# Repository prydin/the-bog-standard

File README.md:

# The Bog Standard - A common sense 50W amplifier for the common (wo)man.

## Background
The idea of this amplifier came from me seeing beginners struggling with amplifier designs 
that were either pure junk, too complicated, required exotic and obsolete components or all of the above.
This sparked a very interesting conversation on diyaudio.com where I presented a previous design
as a candidate. Over the next few weeks, that design got thoroughly critiqued and reworked several times.
As the keen reader will see, the design eventually gravitated towards an architecture that closely
resembles Douglas Self's famous "Blameless Amplifier" concept, albeit using MOSFET output devices rather
than BJTs. 

## Design goals
I had a few overall requirements of the design:
1. Respectable HiFi-grade performance
2. Using only basic, readily available components
3. Being forgiving with respect to component matching
4. No complicated cooling or power supplies needed
5. Being simple enough that someone with modest electronics knowledge can understand its operating principles.

## Component choices
I went with MOSFET output devices because I like the way they sound and they're easy to work with. While
some people suggested rare and expensive lateral MOSFETs, in the spirit of the project, I went with the
good old IRFP(9)240. Based on measurements and listening tests, they perform very well in this setup.

The rest of the transistors are, well, bog standard: 2N5551/2N5401 for low power and BD139/140 for 
medium power. That's it. The rest are just passives and basic diodes.

## Design highlights
As mentioned above, the design follows Doug Self's Blameless Amplifier relatively closely. I went with 
a fairly high loop gain to make sure I had enough to smooth out any non-linearities in the MOSFETs. But
even with all that gain, the amplifier is stable with a 47pF Cdom (and probably 33pF as well, but I was 
out of that value when I tested it). SPICE simulations show about 90 degrees of phase margin with 33pF.

The rest is, you guessed it, Bog Standard. A long-tailed pair differential amplifier at the input section,
a simple single-ended VAS, BJT drivers and MOSFET outputs. The input section and VAS are driven by constant
current sources and the LTP is loaded using a current mirror. The current through the LTP is about 1mA and 
the VAS runs on about 13mA. Q15 offers some basic SOA protection of the VAS. 

The quiescent current is regulated using a standard VBE multiplier controlled by a simple voltage divider.
The design calls for the VBE transistor to be thermally connected to the output devices, by means of 
mounting them on the same heat sink. This gives the amplifier a negative temperature coefficient. 

## Quiescent current setting
I am tentatively running the amplifier on 100mA of quiescent current. This results in an overall power draw
of slighly more than 3W, which seems like a reasonable compromise. Increasing the bias above this didn't 
seem to have any meaningful impact on distortion.

It is very important to let the amplifier warm up before fine tuning the bias. With the VBE multiplier
mounted close to the drivers and outputs, the bias current will have a pronounced negative temperature 
coefficient, so you should expect the quiescent current to be higher on a cold amplifier and then settle.

## Volume control
It's crucial to fit the volume control after the input lowpass filter in order to avoid a frequency response
that varies with the volume. To facilitate this, the PCB comes with a connector for a volume potentiometer. 
I've used 50k pots with good results. If you don't need a volume control at the power amplifier, i.e.
if the amplifier is driven by a preamp, just short pins 2 and 3 on the volume control connector.

## Power supply and grounding
The very simple unregulated power supply that's part of this repository seems to work well and is desined
along the principle of simplicity rather than sophistication. The amplifier itself should have a decent Power
Supply Rejection Ratio (PSRR).

In my build, all grounds (signal, earth and power) meet at the DC side of the power supply and the PCB layout provides
connectors for tying the grounds together. In preliminary tests, there was no audible hum or noise. 

## Transformer
I recommend a 160VA/2x25V toroidial transformer. The actual secondary voltage will vary depending on your mains
voltage, but where I live I get about 35V DC on each rail after rectification. This results in clipping at about
95W in my case, so there's plenty of headroom for the rated 50W. I don't think it would survive sustained 95W power,
at least not without a much larger heatsink than what I have. 

## Case and hardware
The PCBs are compact, so you have a lot of freedom in terms of your physical build. I went for a compact
case from NobSound. It made wire routing a bit challenging and I had to make some compromises. However, the
build came out great without any audible hum or noise. 

### Heat sinks
I'm using a pair of 100 x 40 x 20mm finned heatsinks I found on Amazon. They work well up to about 40W but
get very hot at 50W and above. If your case allows it, I would recommend slightly larger sinks. This is one 
of those situations where bigger really IS better!

## Preliminary performance metrics
* THD @ 1W/1kHz: <0.005%
* Bandwidth (3dB): 20Hz - 900kHz
* Slew rate: 27V/us
* Calculated phase margin: 89 degrees

## Schematic
Click image to enlarge!

## Gerber files
* Amplifier: [kicad/gerber](kicad/gerber)
* Power supply: [kicad/power_supply/gerber](kicad/power_supply/gerber)

## Image gallery

## Contributing
If you find any errors in the design, or if you have ideas how it can be improved, please create an issue report in Github (top menu).
Or even better, clone the repo and issue a PR with your changes and I will consider updating the design using your
modifications.

## About me
I was born in Sweden but live in the US since many years. A software engineer by trade, but I grew up in a home 
full of electronics and test equipment. My father was a very accomplished designer of RF amplifiers for cell towers, so amplifiers 
run in my blood. We had countless conversations over the dinner table about amplifier design. Unfortunately, 
he's no longer with us, but I know he would have loved to follow this project and probably had been very 
opionionated about my design choices...

## Acknowledgements and credits
This work rests on the shoulders of giants. Much of the design is borrowed from Douglas Self's legendary
book "Audio Power Amplifier Design". This is a must-read for anyone interested in audio electronics!
A heartfelt thank you also goes out to the friendly and extremely knowledgeable community at diyaudio.com.
If you haven't joined that site, you should!

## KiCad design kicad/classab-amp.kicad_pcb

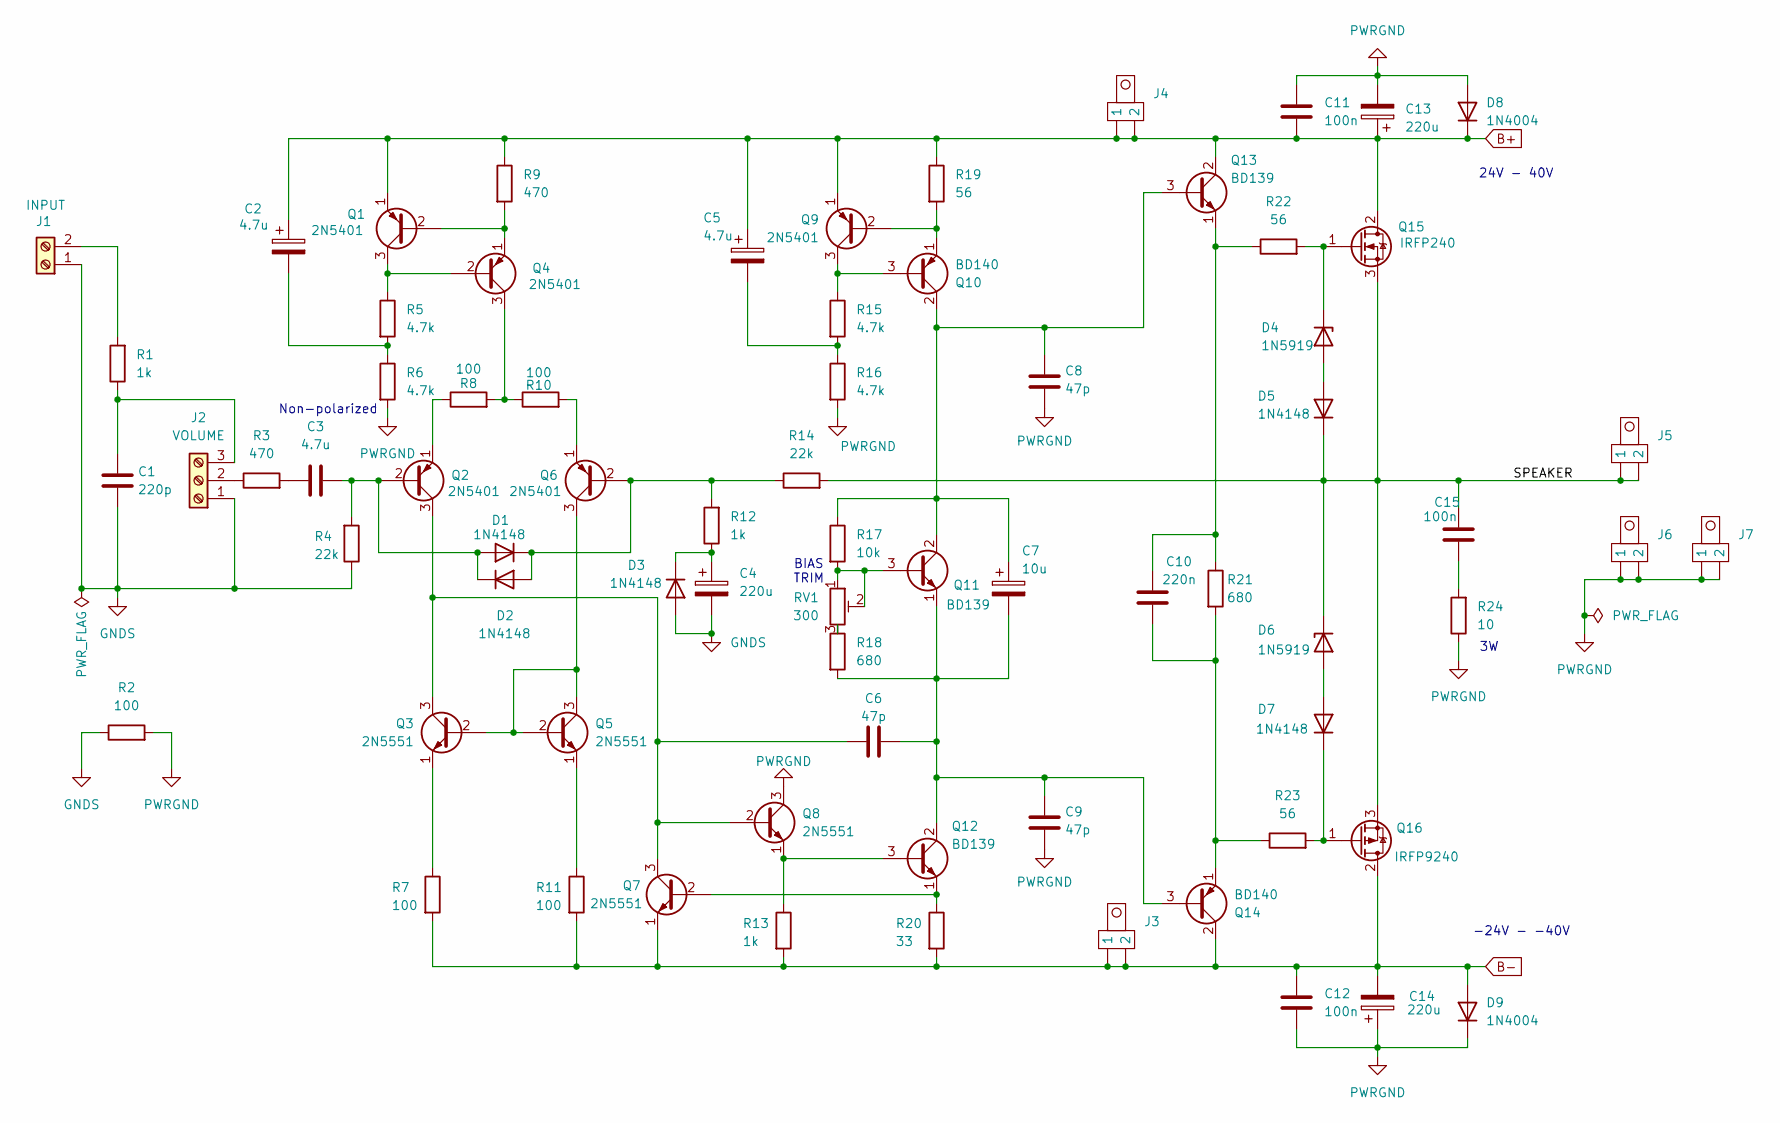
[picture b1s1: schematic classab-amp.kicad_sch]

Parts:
C1: 220p; C_Rect_L7.2mm_W3.0mm_P5.00mm_FKS2_FKP2_MKS2_MKP2
C2, C3, C5: 4.7u; CP_Radial_D4.0mm_P2.00mm
C4, C13, C14: 220u; CP_Radial_D8.0mm_P5.00mm
C6, C8, C9: 47p; C_Rect_L7.2mm_W3.0mm_P5.00mm_FKS2_FKP2_MKS2_MKP2
C7: 10u; CP_Radial_D4.0mm_P2.00mm
C10: 220n; C_Rect_L7.2mm_W3.0mm_P5.00mm_FKS2_FKP2_MKS2_MKP2
C11, C12, C15: 100n; C_Rect_L7.2mm_W3.0mm_P5.00mm_FKS2_FKP2_MKS2_MKP2
D1, D2, D3, D5, D7: 1N4148; D_DO-35_SOD27_P7.62mm_Horizontal
D4, D6: 1N5919; D_DO-41_SOD81_P10.16mm_Horizontal
D8, D9: 1N4004; D_DO-41_SOD81_P10.16mm_Horizontal
J1: INPUT; TerminalBlock_4Ucon_1x02_P3.50mm_Horizontal
J2: VOLUME; TerminalBlock_4Ucon_1x03_P3.50mm_Horizontal
J3, J4, J5, J6, J7: Spade Connector
Q1, Q2, Q4, Q6, Q9: 2N5401; TO-92_Wide
Q3, Q5, Q7, Q8: 2N5551; TO-92_Wide
Q10, Q14: BD140; TO-126-3_Vertical
Q11, Q12, Q13: BD139; TO-126-3_Vertical
Q15: IRFP240; TO-247-3_Vertical
Q16: IRFP9240; TO-247-3_Vertical
R1, R12, R13: 1k; R_Axial_DIN0204_L3.6mm_D1.6mm_P7.62mm_Horizontal
R2, R7, R11: 100; R_Axial_DIN0204_L3.6mm_D1.6mm_P7.62mm_Horizontal
R3, R9: 470; R_Axial_DIN0204_L3.6mm_D1.6mm_P7.62mm_Horizontal
R4, R14: 22k; R_Axial_DIN0204_L3.6mm_D1.6mm_P7.62mm_Horizontal
R5, R6, R15, R16: 4.7k; R_Axial_DIN0204_L3.6mm_D1.6mm_P7.62mm_Horizontal
R8, R10: 100; R_Axial_DIN0207_L6.3mm_D2.5mm_P2.54mm_Vertical
R17: 10k; R_Axial_DIN0207_L6.3mm_D2.5mm_P2.54mm_Vertical
R18: 680; R_Axial_DIN0207_L6.3mm_D2.5mm_P2.54mm_Vertical
R19, R22, R23: 56; R_Axial_DIN0204_L3.6mm_D1.6mm_P7.62mm_Horizontal
R20: 33; R_Axial_DIN0204_L3.6mm_D1.6mm_P7.62mm_Horizontal
R21: 680; R_Axial_DIN0204_L3.6mm_D1.6mm_P7.62mm_Horizontal
R24: 10; R_Axial_DIN0414_L11.9mm_D4.5mm_P5.08mm_Vertical
RV1: 300; TRIM_T93YA103KT20

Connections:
/SPEAKER: C15.1, D5.1 (K), D6.1 (K), J5.1, J5.2, Q15.3 (S), Q16.3 (S), R14.2
B+: C2.1, C5.1, C11.2, C13.1, D8.1 (K), J4.1, J4.2, Q1.1 (E), Q9.1 (E), Q13.2 (C), Q15.2 (D), R9.1, R19.1
B-: C12.1, C14.2, D9.2 (A), J3.1, J3.2, Q7.1 (E), Q14.2 (C), Q16.2 (D), R7.2, R11.2, R13.2, R20.2
GNDS: C1.2, C4.2, D3.2 (A), J1.1, J2.1, R2.1, R4.1
unnamed: C2.2, R5.2, R6.1
unnamed: C3.2, R3.2
unnamed: C5.2, R15.2, R16.1
unnamed: C15.2, R24.2
unnamed: C3.1, D1.2 (A), D2.1 (K), Q2.2 (B), R4.2
unnamed: D1.1 (K), D2.2 (A), Q6.2 (B), R12.2, R14.1
unnamed: C4.1, D3.1 (K), R12.1
unnamed: D4.2 (A), D5.2 (A)
unnamed: D4.1 (K), Q15.1 (G), R22.2
unnamed: D6.2 (A), D7.2 (A)
unnamed: D7.1 (K), Q16.1 (G), R23.2
unnamed: J1.2, R1.2
unnamed: J2.2, R3.1
unnamed: C1.1, J2.3, R1.1
unnamed: Q1.2 (B), Q4.1 (E), R9.2
unnamed: Q1.3 (C), Q4.2 (B), R5.1
unnamed: C6.1, Q2.3 (C), Q3.3 (C), Q7.3 (C), Q8.2 (B)
unnamed: Q2.1 (E), R8.1
unnamed: Q3.2 (B), Q5.2 (B), Q5.3 (C), Q6.3 (C)
unnamed: Q3.1 (E), R7.1
unnamed: Q4.3 (C), R8.2, R10.1
unnamed: Q5.1 (E), R11.1
unnamed: Q6.1 (E), R10.2
unnamed: Q9.3 (C), Q10.3 (B), R15.1
unnamed: C7.1, C8.1, Q10.2 (C), Q11.2 (C), Q13.3 (B), R17.1
unnamed: Q9.2 (B), Q10.1 (E), R19.2
unnamed: Q11.3 (B), R17.2, RV1.1, RV1.2
unnamed: C6.2, C7.2, C9.1, Q11.1 (E), Q12.2 (C), Q14.3 (B), R18.2
unnamed: Q8.1 (E), Q12.3 (B), R13.1
unnamed: Q7.2 (B), Q12.1 (E), R20.1
unnamed: C10.1, Q13.1 (E), R21.1, R22.1
unnamed: C10.2, Q14.1 (E), R21.2, R23.1
unnamed: R18.1, RV1.3
PWRGND: C8.2, C9.2, C11.1, C12.2, C13.2, C14.1, D8.2 (A), D9.1 (K), J6.1, J6.2, J7.1, J7.2, Q8.3 (C), R2.2, R6.2, R16.2, R24.1

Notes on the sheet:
BIAS TRIM
-24V - -40V
24V - 40V
Non-polarized

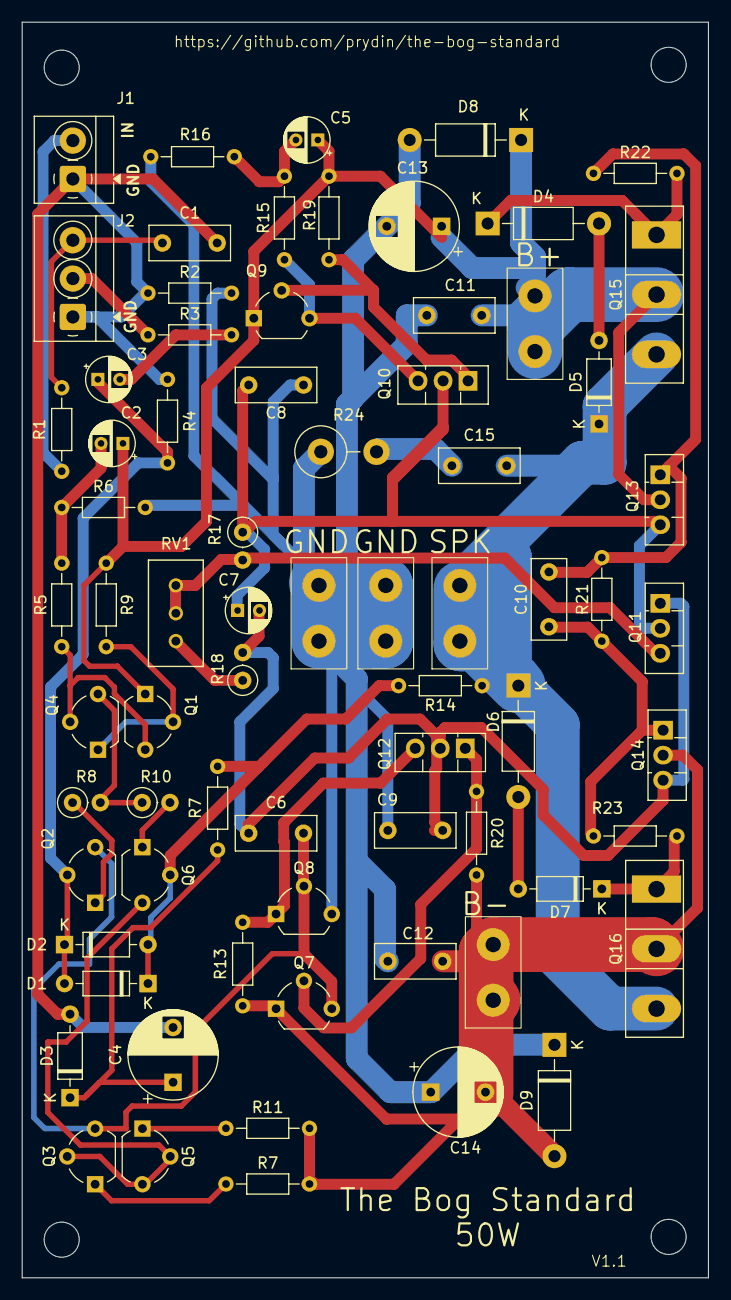
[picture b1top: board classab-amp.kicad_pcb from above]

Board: 2 copper layers, 62.6 x 114.6 mm, 76 parts (0 on the bottom side), 38 nets.

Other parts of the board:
H1, H2, H3, H4: MountingHole_3.2mm_M3

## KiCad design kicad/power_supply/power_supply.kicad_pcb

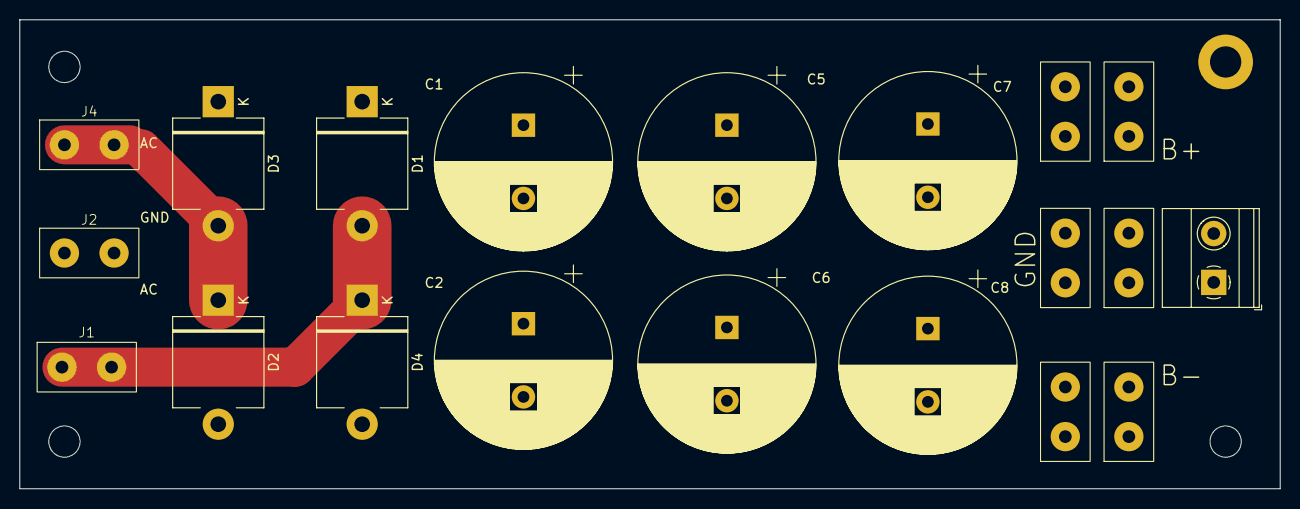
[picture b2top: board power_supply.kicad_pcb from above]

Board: 2 copper layers, 129.0 x 48.0 mm, 20 parts (0 on the bottom side), 5 nets.

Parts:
C1, C2, C5, C6, C7, C8: 4700u; CP_Radial_D18.0mm_P7.50mm
D1, D2, D3, D4: GI754; D_P600_R-6_P12.70mm_Horizontal
J1: AC1; Spade Connector
J2: GND; Spade Connector
J3, J3#2: CT; Spade Connector
J4: AC2; Spade Connector
J5, J5#2: V-; Spade Connector
J6, J6#2: V+; Spade Connector
J7: GND; TerminalBlock_Phoenix_MKDS-1,5-2_1x02_P5.00mm_Horizontal

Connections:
/AC1: D1.2 (A), D4.1 (K), J1.1, J1.2
/AC2: D2.1 (K), D3.2 (A), J4.1, J4.2
/V+: C1.1, C5.1, C7.1, D1.1 (K), D3.1 (K), J6.1, J6.2, J6#2.1, J6#2.2
/V-: C2.2, C6.2, C8.2, D2.2 (A), D4.2 (A), J5.1, J5.2, J5#2.1, J5#2.2
GND: C1.2, C2.1, C5.2, C6.1, C7.2, C8.1, J2.1, J2.2, J3.1, J3.2, J3#2.1, J3#2.2, J7.1, J7.2

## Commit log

2025-02-02 Removed junk files
2025-02-07 Release candidate 1
2025-02-08 Power supply work
2025-02-08 Gerber
2025-02-08 Last minute updates before production
2025-02-18 Adjusted some component positioning
2025-02-23 Added images
2025-02-23 Update gerber files
2025-03-16 V1.1
2025-03-16 Added photos
2025-03-19 Cleaned up SPICE, minor adjustments
2025-03-24 Fixed silkscreen typo
